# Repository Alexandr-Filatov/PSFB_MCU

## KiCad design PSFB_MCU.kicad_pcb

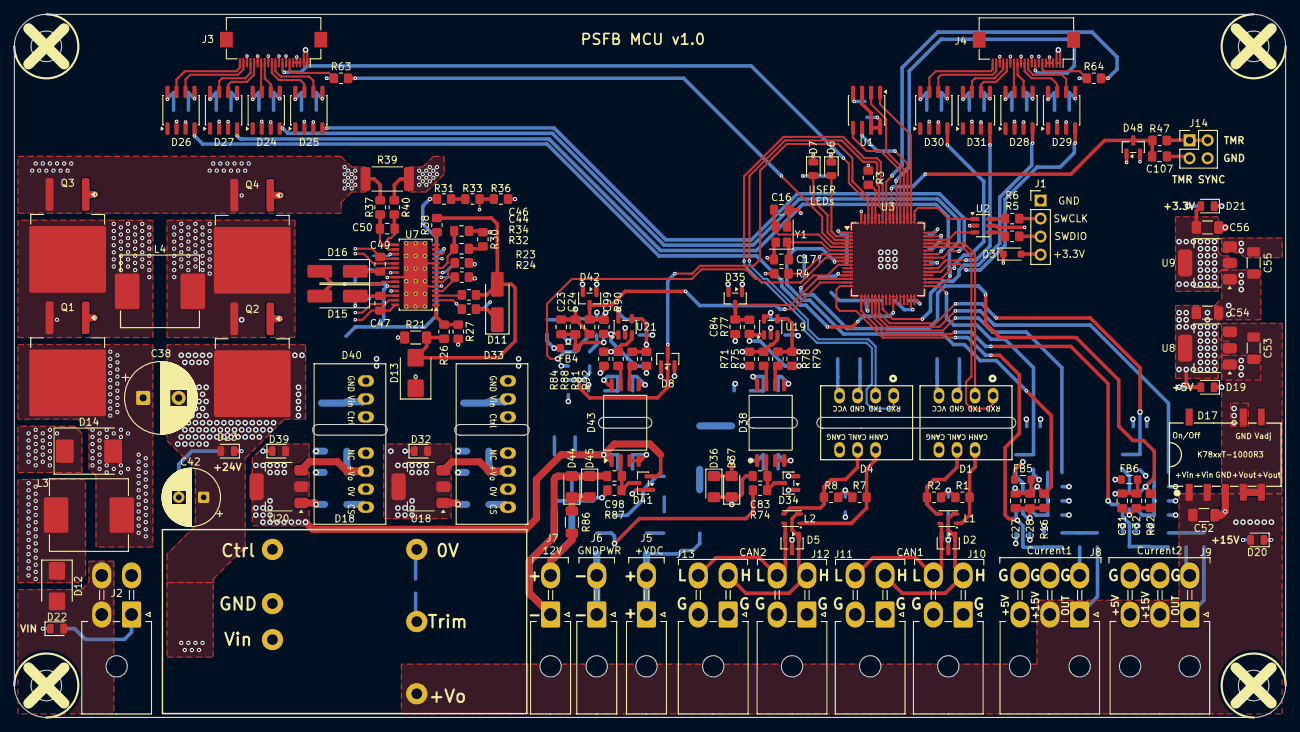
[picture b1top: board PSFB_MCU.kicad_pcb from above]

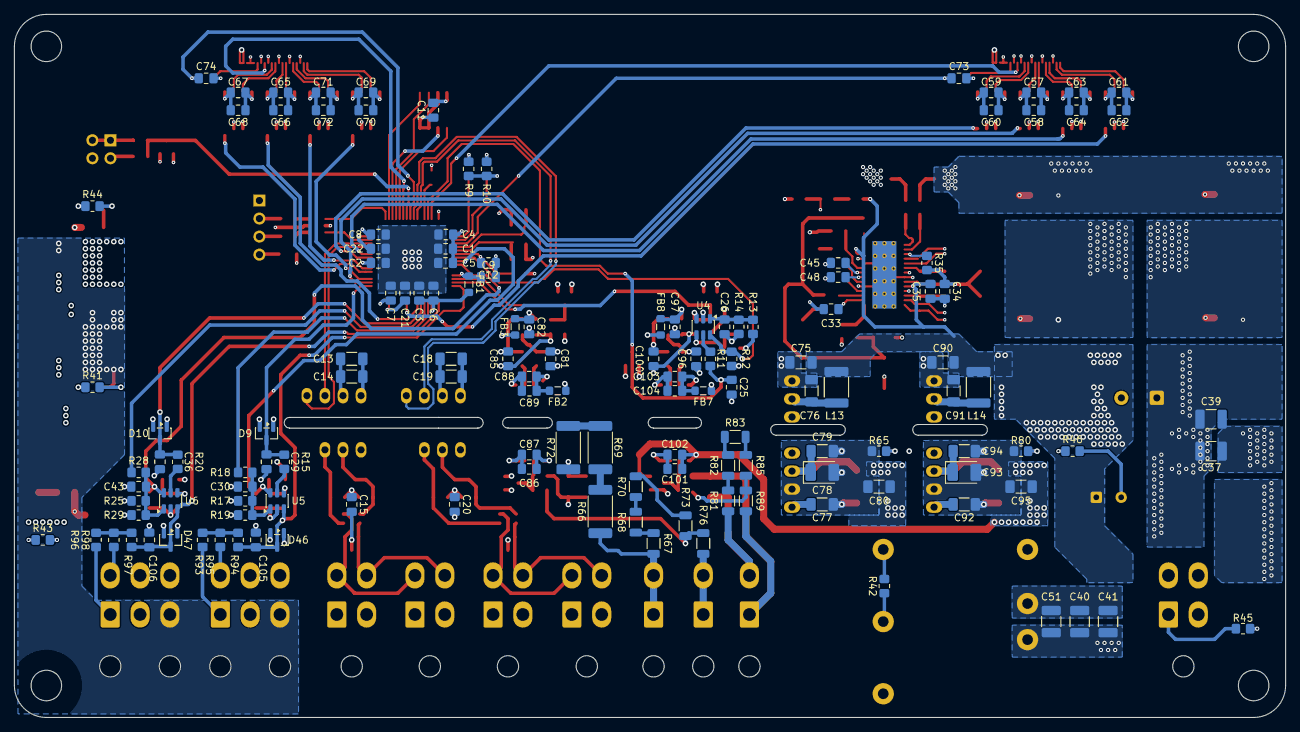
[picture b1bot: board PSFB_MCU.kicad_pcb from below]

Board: 4 copper layers, 179.0 x 99.0 mm, 287 parts (137 on the bottom side), 180 nets.

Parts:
C1, C2, C3, C4, C5, C6, C12, C24, C26, C28, C30, C32, C33, C35, C43, C45, C47, C49, C57, C59, C61, C63, C65, C67, C69, C71, C82, C97: 100n; C_0805_2012Metric_Pad1.18x1.45mm_HandSolder
C7, C58, C60, C62, C64, C66, C68, C70, C72: 4.7u; C_0805_2012Metric_Pad1.18x1.45mm_HandSolder
C8, C11, C34: 1u; C_0805_2012Metric_Pad1.18x1.45mm_HandSolder
C9: 10u; C_0805_2012Metric_Pad1.18x1.45mm_HandSolder
C13, C18, C52, C53, C54, C55, C56, C75, C77, C79, C80, C90, C92, C94, C95: 10u; C_1206_3216Metric_Pad1.33x1.80mm_HandSolder
C14, C19: 100n; C_1206_3216Metric_Pad1.33x1.80mm_HandSolder
C15, C20, C73, C74: 10n; C_0805_2012Metric_Pad1.18x1.45mm_HandSolder
C16, C17: 12p; C_0805_2012Metric_Pad1.18x1.45mm_HandSolder
C21, C22, C23, C27, C31, C86, C88, C101, C103: 2.2u; C_0805_2012Metric_Pad1.18x1.45mm_HandSolder
C25, C29, C36, C107: 10p; C_0805_2012Metric_Pad1.18x1.45mm_HandSolder
C37: 2.2u; C_1210_3225Metric_Pad1.33x2.70mm_HandSolder
C38: 68u; CP_Radial_D10.0mm_P5.00mm
C39: 4.7u; C_1210_3225Metric_Pad1.33x2.70mm_HandSolder
C40, C41, C51: 10u; C_1210_3225Metric_Pad1.33x2.70mm_HandSolder
C42: 220u; CP_Radial_D8.0mm_P3.50mm
C44: 33n; C_0805_2012Metric_Pad1.18x1.45mm_HandSolder
C46: 560p; C_0805_2012Metric_Pad1.18x1.45mm_HandSolder
C48: 220p; C_0805_2012Metric_Pad1.18x1.45mm_HandSolder
C50: 47p; C_0805_2012Metric_Pad1.18x1.45mm_HandSolder
C76, C91: 1u; C_1206_3216Metric_Pad1.33x1.80mm_HandSolder
C78, C93: 100u; CP_EIA-3528-21_Kemet-B_HandSolder
C81, C83, C85, C96, C98, C100: 56p; C_0805_2012Metric_Pad1.18x1.45mm_HandSolder
C84, C99: 1n; C_0805_2012Metric_Pad1.18x1.45mm_HandSolder
C87, C89, C102, C104: 0.1u; C_0805_2012Metric_Pad1.18x1.45mm_HandSolder
C105, C106: 330p; C_0805_2012Metric_Pad1.18x1.45mm_HandSolder
D1, D4: TD5(3)01MCANFD
D2, D5, D8, D9, D10, D34, D35, D41, D42, D46, D47, D48: SOT-23
D3: D_SOD-323_HandSoldering
D6, D7, D19, D20, D21, D22, D23, D32, D39: LED_0805_2012Metric
D11, D15, D16: D_SMA_Handsoldering
D12, D13: D_SMB
D14: D_SMC
D17: K78xxT-1000R3
D18: URB_LD-20WR3
D24, D25, D26, D27, D28, D29, D30, D31: SO-8_3.9x4.9mm_P1.27mm
D33, D40: WRB_S-3WR2
D36, D37, D44, D45: LED_1206_3216Metric_Pad1.42x1.75mm_HandSolder
D38, D43: SOIC-8_7.5x5.85mm_P1.27mm
FB1, FB2, FB3, FB4, FB5, FB6, FB7, FB8: L_0805_2012Metric_Pad1.05x1.20mm_HandSolder
H1, H2, H3, H4: MountingHole; MountingHole_4.3mm_M4
J1: PinHeader_1x04_P2.54mm_Vertical
J2, J10, J11, J12, J13: Molex_Mini-Fit_Jr_5569-04A2_2x02_P4.20mm_Horizontal
J3, J4: Hirose_FH12-20S-0.5SH_1x20-1MP_P0.50mm_Horizontal
J5, J6, J7: Molex_Mini-Fit_Jr_5569-02A2_2x01_P4.20mm_Horizontal
J8, J9: Molex_Mini-Fit_Jr_5569-06A2_2x03_P4.20mm_Horizontal
J14: PinHeader_2x02_P2.54mm_Vertical
L1, L2: L_CommonModeChoke_TDK_ACM2520-2P
L3, L4: 10u; L_Panasonic_PCC-M1040ML
L13, L14: 4.7u; L_1812_4532Metric_Pad1.30x3.40mm_HandSolder
Q1, Q2, Q3, Q4: TO-263-2
R1, R2, R7, R8: 59; R_0805_2012Metric_Pad1.20x1.40mm_HandSolder
R3, R4, R30, R35, R36: 10k; R_0805_2012Metric_Pad1.20x1.40mm_HandSolder
R5, R6: 20; R_0805_2012Metric_Pad1.20x1.40mm_HandSolder
R9, R10, R13, R14, R17, R19, R25, R29, R41, R44, R71, R75, R78, R79, R84, R88, R91, R92: 1k; R_0805_2012Metric_Pad1.20x1.40mm_HandSolder
R11, R15, R20, R37, R40, R47: 100; R_0805_2012Metric_Pad1.20x1.40mm_HandSolder
R12, R16, R18, R22, R28, R38, R42: 0; R_0805_2012Metric_Pad1.20x1.40mm_HandSolder
R21: 10; R_1206_3216Metric_Pad1.30x1.75mm_HandSolder
R23, R93, R96: 2k; R_0805_2012Metric_Pad1.20x1.40mm_HandSolder
R24: 10; R_0805_2012Metric_Pad1.20x1.40mm_HandSolder
R26: 249k; R_0805_2012Metric_Pad1.20x1.40mm_HandSolder
R27: 59k; R_0805_2012Metric_Pad1.20x1.40mm_HandSolder
R31: 240k; R_0805_2012Metric_Pad1.20x1.40mm_HandSolder
R32: 93.1k; R_0805_2012Metric_Pad1.20x1.40mm_HandSolder
R33: 51k; R_0805_2012Metric_Pad1.20x1.40mm_HandSolder
R34: 143k; R_0805_2012Metric_Pad1.20x1.40mm_HandSolder
R39: 10m; R_2512_6332Metric_Pad1.40x3.35mm_HandSolder
R43, R45, R46, R95, R98: 3k; R_0805_2012Metric_Pad1.20x1.40mm_HandSolder
R63, R64: 470; R_0805_2012Metric_Pad1.20x1.40mm_HandSolder
R65, R80: 750; R_0805_2012Metric_Pad1.20x1.40mm_HandSolder
R66, R69, R72: 150k; R_2512_6332Metric_Pad1.40x3.35mm_HandSolder
R67, R68, R70, R73: 2M; R_1206_3216Metric
R74, R87, R94, R97: 120; R_0805_2012Metric_Pad1.20x1.40mm_HandSolder
R76, R89: 11.3k; R_1206_3216Metric
R77, R90: 510; R_0805_2012Metric_Pad1.20x1.40mm_HandSolder
R81, R82, R83, R85: 110k; R_1206_3216Metric
R86: 10k; R_1206_3216Metric_Pad1.30x1.75mm_HandSolder
U1: SOIC-8_3.9x4.9mm_P1.27mm
U2, U4, U5, U6: SOT-23-6
U3: LQFP-64_10x10mm_P0.5mm
U7: HTSSOP-28-1EP_4.4x9.7mm_P0.65mm_EP3.4x9.5mm_ThermalVias
U8, U9, U18, U20: SOT-223-3_TabPin2
U19, U21: SOT-23-5
Y1: 16M; Crystal_SMD_SeikoEpson_FA238-4Pin_3.2x2.5mm

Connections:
+3.3V: C1.1, C2.1, C3.1, C4.1, C5.1, C6.1, C7.1, C8.1, C11.1, C13.1, C14.1, C18.1, C19.1, C56.2, C57.1, C58.1, C59.1, C60.1, C61.1, C62.1, C63.1, C64.1, C65.1, C66.1, C67.1, C68.1, C69.1, C70.1, C71.1, C72.1, D1.4 (VCC), D3.1 (K), D4.4 (VCC), D8.2 (K), D9.2 (K), D10.2 (K), D21.2 (A), D24.3 (DE), D24.8 (VCC), D25.3 (DE), D25.8 (VCC), D26.3 (DE), D26.8 (VCC), D27.3 (DE), D27.8 (VCC), D28.3 (DE), D28.8 (VCC), D29.3 (DE), D29.8 (VCC), D30.3 (DE), D30.8 (VCC), D31.3 (DE), D31.8 (VCC), D35.2 (K), D42.2 (K), D46.2 (K), D47.2 (K), D48.2 (K), FB1.2, FB2.1, FB3.1, FB4.1, FB5.1, FB6.1, FB7.1, FB8.1, R4.1, R13.1, R17.1, R25.1, U1.3 (~WP), U1.7 (~HOLD), U1.8 (VCC), U2.5 (VBUS), U3.1 (VBAT), U3.19 (VDD), U3.32 (VDD), U3.48 (VDD), U3.64 (VDD), U9.2 (VO)
+3.3VA: C9.1, FB1.1, U3.13 (VDDA)
+3.3VP: C80.2, C86.2, C87.1, D32.2 (A), D34.2 (K), D38.1 (VDD1), U18.2 (VO)
+3V3: C95.2, C101.2, C102.1, D39.2 (A), D41.2 (K), D43.1 (VDD1), U20.2 (VO)
+5V: C54.2, C55.2, D19.2 (A), J8.3, J9.3, U8.2 (VO), U9.3 (VI)
+9V: C53.2, D17.4 (+Vout), D17.5 (+Vout), U8.3 (VI)
+15V: C52.2, D17.1 (+Vin), D17.2 (+Vin), D18.4 (+Vo), D20.2 (A), J3.1, J3.2, J4.1, J4.2, J8.2, J9.2
+24V: C35.1, C40.2, C41.2, C42.1, C51.2, C75.1, C90.1, D18.3 (Vin), D23.2 (A), L13.1, L14.1, Q2.2 (D), R31.2, U7.12 (VOSNS), U7.24 (BIAS)
/BkIN_1: C29.1, D9.3 (common), R15.1, U3.33 (PB12)
/BkIN_8: C36.1, D10.3 (common), R20.1, U3.22 (PA6)
/CAN1_RXD_MCU: D1.1 (RXD), U3.44 (PA11)
/CAN1_TXD_MCU: D1.2 (TXD), U3.45 (PA12)
/CAN2_RXD_MCU: D4.1 (RXD), U3.57 (PB5)
/CAN2_TXD_MCU: D4.2 (TXD), U3.58 (PB6)
/CANH_1: D2.1 (K), J10.3, J11.3, L1.2
/CANH_2: D5.1 (K), J12.3, J13.3, L2.2
/CANL_1: D2.2 (K), J10.4, J11.4, L1.4
/CANL_2: D5.2 (K), J12.4, J13.4, L2.4
/Connector_channel_1/ERROR: J3.6, R63.1
/Connector_channel_1/PWM_H1_N: D25.7 (B), J3.11
/Connector_channel_1/PWM_H1_P: D25.6 (A), J3.10
/Connector_channel_1/PWM_H2_N: D27.7 (B), J3.17
/Connector_channel_1/PWM_H2_P: D27.6 (A), J3.16
/Connector_channel_1/PWM_L1_N: D24.7 (B), J3.14
/Connector_channel_1/PWM_L1_P: D24.6 (A), J3.13
/Connector_channel_1/PWM_L2_N: D26.7 (B), J3.20
/Connector_channel_1/PWM_L2_P: D26.6 (A), J3.19
/Connector_channel_2/ERROR: J4.6, R64.1
/Connector_channel_2/PWM_H1_N: D29.7 (B), J4.11
/Connector_channel_2/PWM_H1_P: D29.6 (A), J4.10
/Connector_channel_2/PWM_H2_N: D31.7 (B), J4.17
/Connector_channel_2/PWM_H2_P: D31.6 (A), J4.16
/Connector_channel_2/PWM_L1_N: D28.7 (B), J4.14
/Connector_channel_2/PWM_L1_P: D28.6 (A), J4.13
/Connector_channel_2/PWM_L2_N: D30.7 (B), J4.20
/Connector_channel_2/PWM_L2_P: D30.6 (A), J4.19
/Current_measure1/Current_sense_1: J8.1, R93.1
/Current_measure1/Current_sense_2: J9.1, R96.1
/Current_measure_1: C105.1, D46.3 (common), R94.1, U3.16 (PA2), U5.3 (+)
/Current_measure_2: C106.1, D47.3 (common), R97.1, U3.17 (PA3), U6.3 (+)
/DAC1: R18.1, U3.20 (PA4)
/DAC2: R28.1, U3.21 (PA5)
/EEPROM_MISO_MCU: U1.2 (MISO), U3.52 (PC11)
/EEPROM_MOSI_MCU: U1.5 (MOSI), U3.53 (PC12)
/EEPROM_SCK_MCU: U1.6 (SCK), U3.51 (PC10)
/EEPROM_~CS_MCU: U1.1 (~CS), U3.50 (PA15)
/ERROR_Channel_1: C73.1, R63.2, U3.4 (PC15)
/ERROR_Channel_2: C74.1, R64.2, U3.56 (PB4)
/HDRV1: Q1.1 (G), U7.27 (HDRV1)
/HDRV2: Q2.1 (G), U7.19 (HDRV2)
/HVDC_MCU: C84.1, D35.3 (common), R77.2, U3.14 (PA0)
/LDRV1: Q3.1 (G), U7.25 (LDRV1)
/LDRV2: Q4.1 (G), U7.21 (LDRV2)
/LVDC_MCU: C99.1, D42.3 (common), R90.2, U3.15 (PA1), U4.3 (+)
/OverVoltage: C25.1, D8.3 (common), R11.1, U3.61 (PB8)
/RST_Channel_1: J3.8, U3.62 (PB9)
/RST_Channel_2: J4.8, U3.54 (PD2)
/SHDN_OverCurrent_1: R16.2, U3.9 (PC1), U5.6 (SHDN)
/SHDN_OverCurrent_2: R22.2, U3.10 (PC2), U6.6 (SHDN)
/SHDN_OverVoltage: R12.2, U3.8 (PC0), U4.6 (SHDN)
/SW1: C47.1, L4.1, Q1.3 (S), Q3.2 (D), U7.28 (SW1)
/SW2: C49.1, L4.2, Q2.3 (S), Q4.2 (D), U7.18 (SW2)
/SWCLK: U2.1 (I/O1), U3.49 (PA14)
/SWDIO: U2.3 (I/O2), U3.46 (PA13)
/TMR1_CH1: D25.4 (DI), U3.41 (PA8)
/TMR1_CH1N: D24.4 (DI), U3.34 (PB13)
/TMR1_CH2: D27.4 (DI), U3.42 (PA9)
/TMR1_CH2N: D26.4 (DI), U3.26 (PB0)
/TMR2_CH2_SYNC: C107.1, D48.3 (common), R47.1, U3.55 (PB3)
/TMR8_CH1: D29.4 (DI), U3.37 (PC6)
/TMR8_CH1N: D28.4 (DI), U3.23 (PA7)
/TMR8_CH2: D31.4 (DI), U3.38 (PC7)
/TMR8_CH2N: D30.4 (DI), U3.35 (PB14)
BOOT0: R3.2, U3.60 (BOOT0)
GND: C1.2, C2.2, C3.2, C4.2, C5.2, C6.2, C7.2, C8.2, C9.2, C11.2, C12.1, C13.2, C14.2, C16.1, C17.2, C18.2, C19.2, C21.2, C22.2, C23.2, C24.2, C25.2, C26.2, C27.2, C28.2, C29.2, C30.2, C31.2, C32.2, C36.2, C43.2, C52.1, C53.1, C54.1, C55.1, C56.1, C57.2, C58.2, C59.2, C60.2, C61.2, C62.2, C63.2, C64.2, C65.2, C66.2, C67.2, C68.2, C69.2, C70.2, C71.2, C72.2, C73.2, C74.2, C81.1, C82.2, C84.2, C88.1, C89.2, C96.1, C97.2, C99.2, C103.1, C104.2, C105.2, C106.2, C107.2, D1.3 (GND), D4.3 (GND), D8.1 (A), D9.1 (A), D10.1 (A), D17.3 (GND), D17.7 (GND), D18.6 (0V), D24.2 (~RE), D24.5 (GND), D25.2 (~RE), D25.5 (GND), D26.2 (~RE), D26.5 (GND), D27.2 (~RE), D27.5 (GND), D28.2 (~RE), D28.5 (GND), D29.2 (~RE), D29.5 (GND), D30.2 (~RE), D30.5 (GND), D31.2 (~RE), D31.5 (GND), D35.1 (A), D38.5 (GND2), D42.1 (A), D43.5 (GND2), D46.1 (A), D47.1 (A), D48.1 (A), J1.1, J3.3, J3.4, J3.5, J3.7, J3.9, J3.12, J3.15, J3.18, J4.3, J4.4, J4.5, J4.7, J4.9, J4.12, J4.15, J4.18, J8.4, J8.5, J8.6, J9.4, J9.5, J9.6, J14.3, J14.4, R3.1, R9.2, R10.2, R12.1, R14.2, R16.1, R19.2, R22.1, R29.2, R41.2, R42.2, R43.2, R44.2, R71.1, R84.1, R95.2, R98.2, U1.4 (GND), U2.2 (GND), U3.12 (VSSA), U3.18 (VSS), U3.63 (VSS), U4.2 (V-), U5.2 (V-), U6.2 (V-), U8.1 (GND), U9.1 (GND), U19.2 (V-), U21.2 (V-), Y1.2, Y1.4
GNDPWR: C77.1, C78.2, C79.1, C80.1, C83.2, C86.1, C87.2, D33.7 (0V), D34.1 (A), D36.2 (A), D37.1 (K), D38.3 (SHTDN), D38.4 (GND1), J6.1, J6.2, R65.2, R76.1, U18.1 (GND)
GND_CAN1: C15.2, D1.5 (CANG), D2.3 (A), J10.1, J10.2, J11.1, J11.2
GND_CAN2: C20.2, D4.5 (CANG), D5.3 (A), J12.1, J12.2, J13.1, J13.2
GND_IN: C33.2, C34.2, C35.2, C37.1, C38.2, C39.1, C40.1, C41.1, C42.2, C45.2, C46.2, C48.2, C51.1, C75.2, C76.2, C90.2, C91.2, D13.1 (A1), D14.1 (A1), D18.2 (GND), D33.1 (GND), D40.1 (GND), J2.1, J2.3, R27.2, R30.1, R32.1, R34.2, R36.2, R39.1, R40.1, R45.2, R46.2, U7.5 (DITH), U7.10 (AGND), U7.22 (PGND), U7.29 (PowerPAD)
GND_OUT: C92.1, C93.2, C94.1, C95.1, C98.2, C101.1, C102.2, D40.7 (0V), D41.1 (A), D43.3 (SHTDN), D43.4 (GND1), D44.2 (A), D45.1 (K), J7.1, R80.2, R89.1, U20.1 (GND)
NRST: C12.2, R4.2, U3.7 (NRST)
unnamed: C15.1, R1.1, R2.2
unnamed: C20.1, R7.1, R8.2
unnamed: C44.2, R30.2
unnamed: C85.2, R77.1, R79.2, U19.1
unnamed: C100.2, R90.1, R92.2, U21.1
unnamed: D1.7 (CANH), L1.1, R1.2
unnamed: D1.6 (CANL), L1.3, R2.1
unnamed: D3.2 (A), J1.4
unnamed: D4.7 (CANH), L2.1, R7.2
unnamed: D4.6 (CANL), L2.3, R8.1
unnamed: D6.2 (A), U3.2 (PC13)
unnamed: D6.1 (K), R9.1
unnamed: D7.2 (A), U3.3 (PC14)
unnamed: D7.1 (K), R10.1
unnamed: D11.1 (K), R24.2
unnamed: D12.1 (K), L3.1
unnamed: C37.2, C38.1, C39.2, D14.2 (A2), L3.2, Q1.2 (D), R21.1
unnamed: C47.2, D15.1 (K), U7.26 (BOOT1)
unnamed: C49.2, D16.1 (K), U7.20 (BOOT2)
unnamed: D18.5 (Trim), R42.1
unnamed: D19.1 (K), R41.1
unnamed: D20.1 (K), R43.1
unnamed: D21.1 (K), R44.1
unnamed: D22.1 (K), R45.1
unnamed: D23.1 (K), R46.1
unnamed: D32.1 (K), R65.1
unnamed: C78.1, C79.2, D33.6 (+Vo), U18.3 (VI)
unnamed: C77.2, D33.8 (CS)
unnamed: C76.1, D33.2 (Vin), L13.2
unnamed: C83.1, D34.3 (common), D38.2 (VIN), R74.1
unnamed: D36.1 (K), D37.2 (A), R72.2
unnamed: D38.6 (OUTN), R78.1
unnamed: D38.7 (OUTP), R75.1
unnamed: C88.2, C89.1, D38.8 (VDD2), FB2.2
unnamed: D39.1 (K), R80.1
unnamed: C93.1, C94.2, D40.6 (+Vo), U20.3 (VI)
unnamed: C92.2, D40.8 (CS)
unnamed: C91.1, D40.2 (Vin), L14.2
unnamed: C98.1, D41.3 (common), D43.2 (VIN), R87.1
unnamed: D43.6 (OUTN), R91.1
unnamed: D43.7 (OUTP), R88.1
unnamed: C103.2, C104.1, D43.8 (VDD2), FB7.2
unnamed: D44.1 (K), D45.2 (A), R86.2
unnamed: J1.2, R6.2
unnamed: J1.3, R5.2
unnamed: J5.1, J5.2, R66.1, R67.2
unnamed: J7.2, R81.2, R86.1
unnamed: J14.1, J14.2, R47.2
unnamed: Q3.3 (S), Q4.3 (S), R37.1, R39.2
unnamed: R5.1, U2.4 (I/O2)
unnamed: R6.1, U2.6 (I/O1)
unnamed: R11.2, U4.5
unnamed: R15.2, U5.5
unnamed: R20.2, U6.5
unnamed: R31.1, R33.2
unnamed: R66.2, R69.1
unnamed: R67.1, R68.2
unnamed: R68.1, R70.2
unnamed: R69.2, R72.1
unnamed: R70.1, R73.2
unnamed: R73.1, R74.2, R76.2
unnamed: R81.1, R82.2
unnamed: R82.1, R83.2
unnamed: R83.1, R85.2
unnamed: R85.1, R87.2, R89.2
unnamed: R93.2, R94.2, R95.1
unnamed: R96.2, R97.2, R98.1
unnamed: C16.2, U3.5 (PH0), Y1.3
unnamed: C17.1, U3.6 (PH1), Y1.1
unnamed: C21.1, U3.31 (VCAP_1)
unnamed: C22.1, U3.47 (VCAP_2)
unnamed: C26.1, R13.2, R14.1, U4.1 (-)
unnamed: C23.1, C24.1, FB4.2, U4.4 (V+)
unnamed: C30.1, R17.2, R18.2, R19.1, U5.1 (-)
unnamed: C27.1, C28.1, FB5.2, U5.4 (V+)
unnamed: C43.1, R25.2, R28.2, R29.1, U6.1 (-)
unnamed: C31.1, C32.1, FB6.2, U6.4 (V+)
unnamed: C44.1, C46.1, U7.9 (COMP)
unnamed: C50.2, R37.2, U7.16 (CS)
unnamed: C50.1, R40.2, U7.15 (CSG)
unnamed: R26.1, R27.1, U7.1 (EN/UVLO)
unnamed: R33.1, R36.1, U7.11 (FB)
unnamed: R38.1, U7.13 (ISNS(-)), U7.14 (ISNS(+))
unnamed: R32.2, U7.4 (MODE)
unnamed: R35.1, U7.17 (PGOOD)
unnamed: R34.1, U7.6 (RT/SYNC)
unnamed: C48.1, U7.7 (SLOPE)
unnamed: C45.1, U7.8 (SS)
unnamed: C33.1, R24.1, U7.2 (VIN)
unnamed: R23.2, U7.3 (VISNS)
unnamed: C81.2, R71.2, R75.2, U19.3 (+)
unnamed: C85.1, R78.2, R79.1, U19.4 (-)
unnamed: C82.1, FB3.2, U19.5 (V+)
unnamed: C96.2, R84.2, R88.2, U21.3 (+)
unnamed: C100.1, R91.2, R92.1, U21.4 (-)
unnamed: C97.1, FB8.2, U21.5 (V+)
VCC: C34.1, D15.2 (A), D16.2 (A), R35.2, U7.23 (VCC)
VIN: D12.2 (A), D22.2 (A), J2.2, J2.4
VIN_filtered: D11.2 (A), D13.2 (A2), R21.2, R23.1, R26.2, R38.2

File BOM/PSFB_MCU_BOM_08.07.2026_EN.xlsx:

Reference | Value | Product Name | Replacement | Package | Description | Quantity | DNP
C87, C89, C102, C104 | 0.1u |  |  | SMD 0805 | Capacitor SMD 25V | 4
C1, C2, C3, C4, C5, C6, C12, C24, C26, C28, C30, C32, C33, C35, C43, C45, C47, 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 | 100n |  |  | SMD 0805 | Capacitor SMD 25V | 28
C14, C19 | 100n |  |  | SMD 1206 | Capacitor SMD 25V | 2
C78, C93 | 100u | 6TPE100MWB |  | CP EIA-3528-21 Kemet-B | Capacitor tantalum SMD 6.3V | 2
C15, C20, C73, C74 | 10n |  |  | SMD 0805 | Capacitor SMD 25V | 4
C25, C29, C36, C107 | 10p |  |  | SMD 0805 | Capacitor SMD 25V | 4
C9 | 10u |  |  | SMD 0805 | Capacitor SMD 25V | 1
C13, C18, C54, C55, C56, C75, C77, C79, C80, C90, C92, C94, C95 | 10u |  |  | SMD 1206 | Capacitor SMD 25V | 13
C52, C53 | 10u |  |  | SMD 1206 | Capacitor SMD 50V | 2
C40, C41, C51 | 10u |  |  | SMD 1210 | Capacitor SMD 50V | 3
C16, C17 | 12p |  |  | SMD 0805 | Capacitor SMD 25V | 2
C84, C99 | 1n |  |  | SMD 0805 | Capacitor SMD 25V | 2
C8, C11, C34 | 1u |  |  | SMD 0805 | Capacitor SMD 25V | 3
C76, C91 | 1u |  |  | SMD 1206 | Capacitor SMD 50V | 2
C21, C22, C23, C27, C31, C86, C88, C101, C103 | 2.2u |  |  | SMD 0805 | Capacitor SMD 25V | 9
C37 | 2.2u |  |  | SMD 1210 | Capacitor SMD 100V | 1
C48 | 220p |  |  | SMD 0805 | Capacitor SMD 25V | 1
C42 | 220u | EEUFM1V221L |  | CP Radial D8.0mm P3.50mm | Capacitor electrolytic low ESR | 1
C105, C106 | 330p |  |  | SMD 0805 | Capacitor SMD 25V | 2
C44 | 33n |  |  | SMD 0805 | Capacitor SMD 25V | 1
C7, C58, C60, C62, C64, C66, C68, C70, C72 | 4.7u |  |  | SMD 0805 | Capacitor SMD 25V | 9
C39 | 4.7u |  |  | SMD 1210 | Capacitor SMD 100V | 1
C50 | 47p |  |  | SMD 0805 | Capacitor SMD 25V | 1
C46 | 560p |  |  | SMD 0805 | Capacitor SMD 25V | 1
C81, C83, C85, C96, C98, C100 | 56p |  |  | SMD 0805 | Capacitor SMD 25V | 6
C38 | 68u | EEUFC2A680 |  | CP Radial D10.0mm P5.00mm | Capacitor electrolytic low ESR | 1
D17 | ~ | K7809T |  | K78xxT-1000R3 | DC/DC | 1
D11, D15, D16 | ~ | US1B |  | SMA | Diode | 3
D12 | ~ | GS3MB |  | SMB | Diode | 1
D13 | ~ | SMBJ51A |  | SMB | TVS | 1
D14 | ~ | SMCJ58A |  | SMC | TVS | 1
D6, D7 | ~ | FYLS-0603UBC |  | SMD 0805 | Blue LED | 2
D19, D20, D21, D22, D23, D32, D39 | ~ | FYLS-0805UYC |  | SMD 0805 | Yellow LED | 7
D37, D45 | ~ | TO-3216BC-PG |  | SMD 1206 | Green LED | 2
D36, D44 | ~ | TO-3216BC-MRE |  | SMD 1206 | Red LED | 2
D24, D25, D26, D27, D28, D29, D30, D31 | ~ | MS2111 |  | SO-8 3.9x4.9mm P1.27mm | LVDS | 8
D3 | ~ | LBAT54HT1G |  | SOD-323 | Diode | 1
D38, D43 | ~ | NSI1311 |  | SOIC-8 7.5x5.85mm P1.27mm | Isolated amplifier | 2
D2, D5 | ~ | SM24CANB-02HTG |  | SOT-23 | Dual Line CAN Bus Protector, 24Vrwm | 2
D8, D9, D10, D34, D35, D41, D42, D46, D47, D48 | ~ | BAT54S |  | SOT-23 | Schottky barrier diode | 10
D1, D4 | ~ | TD301MCANFD |  | TD5(3)01MCANFD | CAN transiever | 2
D18 | ~ | URB2415LD-20WR3 |  | URB LD-20WR3 | DC/DC | 1
D33, D40 | ~ | WRB2405S-3WR2 |  | WRB S-3WR2 | DC/DC | 2
FB1, FB2, FB3, FB4, FB5, FB6, FB7, FB8 | ~ | MMZ2012R301AT000 |  | SMD 0805 | Ferrite bead | 8
J3, J4 | ~ | FH12-20S-0.5SH |  | Hirose FH12-20S-0.5SH 1x20-1MP P0.50mm | Connector | 2
J5, J6, J7 | ~ | DS1073-01-2x1MR2T6 |  | Molex Mini-Fit Jr 5569-02A2 2x01 P4.20mm | Connector | 3
J2, J10, J11, J12, J13 | ~ | DS1073-01-2x2MR2T6 |  | Molex Mini-Fit Jr 5569-04A2 2x02 P4.20mm | Connector | 5
J8, J9 | ~ | DS1073-01-2x3MR2T6 |  | Molex Mini-Fit Jr 5569-06A2 2x03 P4.20mm | Connector | 2
J1 | ~ | KLS1-207-1-04-S | DS-1021-1x4 | PinHeader 1x04 P2.54mm | Connector | 1
J14 | ~ | DS1021-2x2SF11 |  | PinHeader 2x02 P2.54mm | Connector | 1
L3, L4 | 10u | ETQP4M100KVC |  | Panasonic PCC-M1040ML | Inductor SMD | 2
L13, L14 | 4.7u | NLC453232T-4R7K-PF |  | SMD 1812 | Inductor SMD | 2
L1, L2 | ~ | ACM2520-301-2P-T002 |  | CommonModeChoke TDK ACM2520-2P | Inductor SMD | 2
Q1, Q2, Q3, Q4 | ~ | WMM043N10HGD |  | TO-263-2 | MOSFET | 4
R38 | 0 |  |  | SMD 0805 | Resistor SMD 1% | 1
R12, R16, R18, R22, R28, R42 | 0 |  |  | SMD 0805 | Resistor SMD 1% | 6 | ✓
R24 | 10 |  |  | SMD 0805 | Resistor SMD 1% | 1
R21 | 10 | ERJP08F10R0V |  | SMD 1206 | Resistor SMD 1% | 1
R11, R15, R20, R37, R40, R47 | 100 |  |  | SMD 0805 | Resistor SMD 1% | 6
R3, R4, R30, R35, R36 | 10k |  |  | SMD 0805 | Resistor SMD 1% | 5
R86 | 10k |  |  | SMD 1206 | Resistor SMD 1% | 1
R39 | 10m |  |  | SMD 2512 | Resistor SMD 1% | 1
R76, R89 | 11.3k |  |  | SMD 1206 | Resistor SMD 0.1% | 2
R81, R82, R83, R85 | 110k |  |  | SMD 1206 | Resistor SMD 0.1% | 4
R74, R87, R94, R97 | 120 |  |  | SMD 0805 | Resistor SMD 1% | 4
R34 | 143k |  |  | SMD 0805 | Resistor SMD 1% | 1
R66, R69, R72 | 150k |  |  | SMD 2512 | Resistor SMD 1% | 3
R9, R10, R13, R14, R17, R19, R25, R29, R41, R44, R71, R75, R78, R79, R84, R88, 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 | 1k |  |  | SMD 0805 | Resistor SMD 1% | 18
R5, R6 | 20 |  |  | SMD 0805 | Resistor SMD 1% | 2
R31 | 240k |  |  | SMD 0805 | Resistor SMD 1% | 1
R26 | 249k |  |  | SMD 0805 | Resistor SMD 1% | 1
R67, R68, R70, R73 | 2M |  |  | SMD 1206 | Resistor SMD 0.1% | 4
R93, R96 | 2k |  |  | SMD 0805 | Resistor SMD 0.1% | 2
R23 | 2k |  |  | SMD 0805 | Resistor SMD 1% | 1
R95, R98 | 3k |  |  | SMD 0805 | Resistor SMD 0.1% | 2
R43, R45, R46 | 3k |  |  | SMD 0805 | Resistor SMD 1% | 3
R63, R64 | 470 |  |  | SMD 0805 | Resistor SMD 1% | 2
R77, R90 | 510 |  |  | SMD 0805 | Resistor SMD 1% | 2
R33 | 51k |  |  | SMD 0805 | Resistor SMD 1% | 1
R1, R2, R7, R8 | 59 |  |  | SMD 0805 | Resistor SMD 1% | 4
R27 | 59k |  |  | SMD 0805 | Resistor SMD 1% | 1
R65, R80 | 750 |  |  | SMD 0805 | Resistor SMD 1% | 2
R32 | 93.1k |  |  | SMD 0805 | Resistor SMD 1% | 1
U7 | ~ | LM5176PWP |  | HTSSOP-28-1EP 4.4x9.7mm P0.65mm EP3.4x9.5mm | DC/DC | 1
U3 | ~ | APM32F405RGT6 |  | LQFP-64 10x10mm P0.5mm | MCU | 1
U1 | ~ | FM25W256 |  | SOIC-8 3.9x4.9mm P1.27mm | FRAM | 1
U9 | ~ | AMS1117-3.3 |  | SOT-223-3 | Linear regulator | 1
U8 | ~ | AMS1117-5.0 |  | SOT-223-3 | Linear regulator | 1
U18, U20 | ~ | TLV1117LV33DCYR |  | SOT-223-3 | Linear regulator | 2
U19, U21 | ~ | OPA333AIDBVR |  | SOT-23-5 | Op-Amp | 2
U4, U5, U6 | ~ | TLV3501AIDBV |  | SOT-23-6 | Comparator | 3
U2 | ~ | USBLC6-2SC6 |  | SOT-23-6 | ESD protection | 1
Y1 | 16M | X322516MOB4SI |  | Crystal SMD SeikoEpson FA238-4Pin 3.2x2.5mm | Crystal | 1

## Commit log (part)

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2026-04-23 Zero commit
2026-04-23 VER1.0: убрал лишнее, добавил на схему питание 5В
2026-04-28 VER1.0: убрал лишние сигналы и доделал 5В
2026-04-28 VER1.0: надо разобраться с питанием 9-60В
2026-05-22 VER1.0: собрал всю цепь питания на схеме
2026-05-25 VER1.0: добавил 4 канала управления драйверами
2026-06-16 VER1.0: добавил схему с измерением напряжения и заменил LVDS трансиверы
2026-06-18 VER1.0: добавил аппаратную защиту
2026-06-21 VER1.0: добавил защиту бортового питания для тестов по ISO 7637-2 (Степень III)
2026-06-22 VER1.0: добавил разъемы для платы вторички
2026-06-24 VER1.0: добавил разделение питания VDD и VDDA
2026-06-29 VER1.0: раскидал компоненты на плате
2026-06-29 VER1.0: отредактировал BOM
